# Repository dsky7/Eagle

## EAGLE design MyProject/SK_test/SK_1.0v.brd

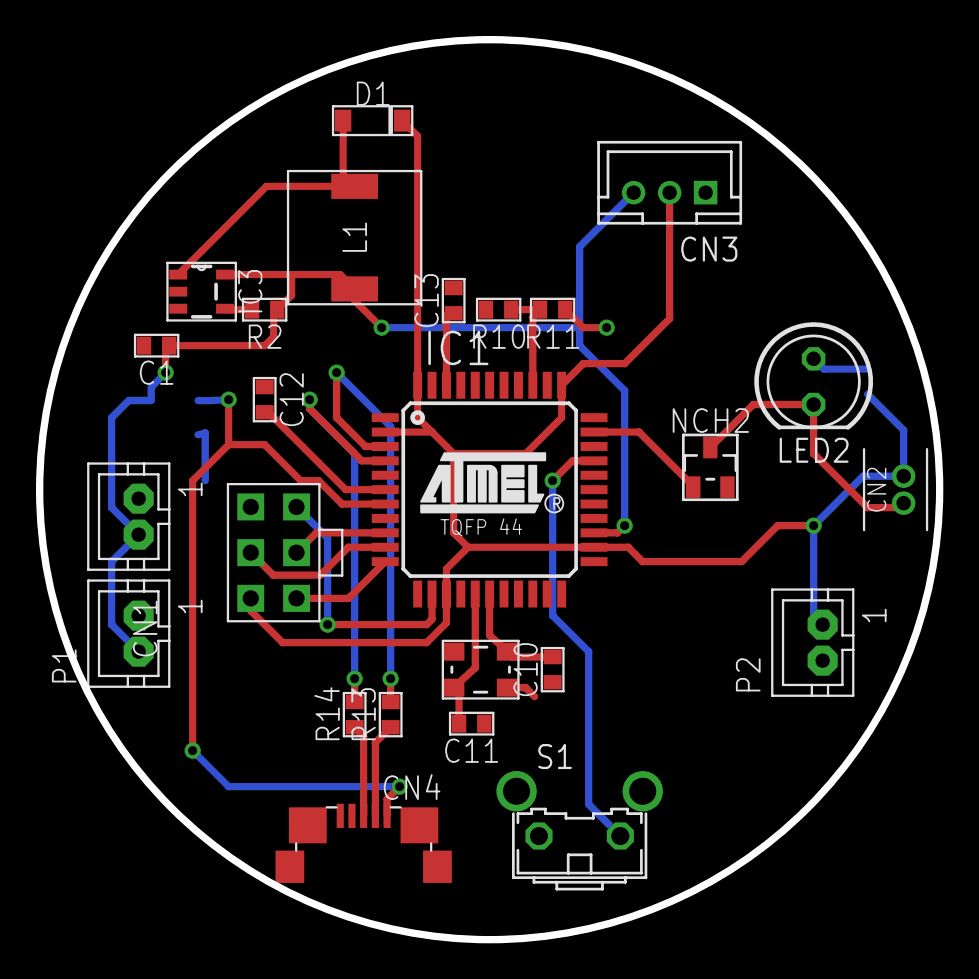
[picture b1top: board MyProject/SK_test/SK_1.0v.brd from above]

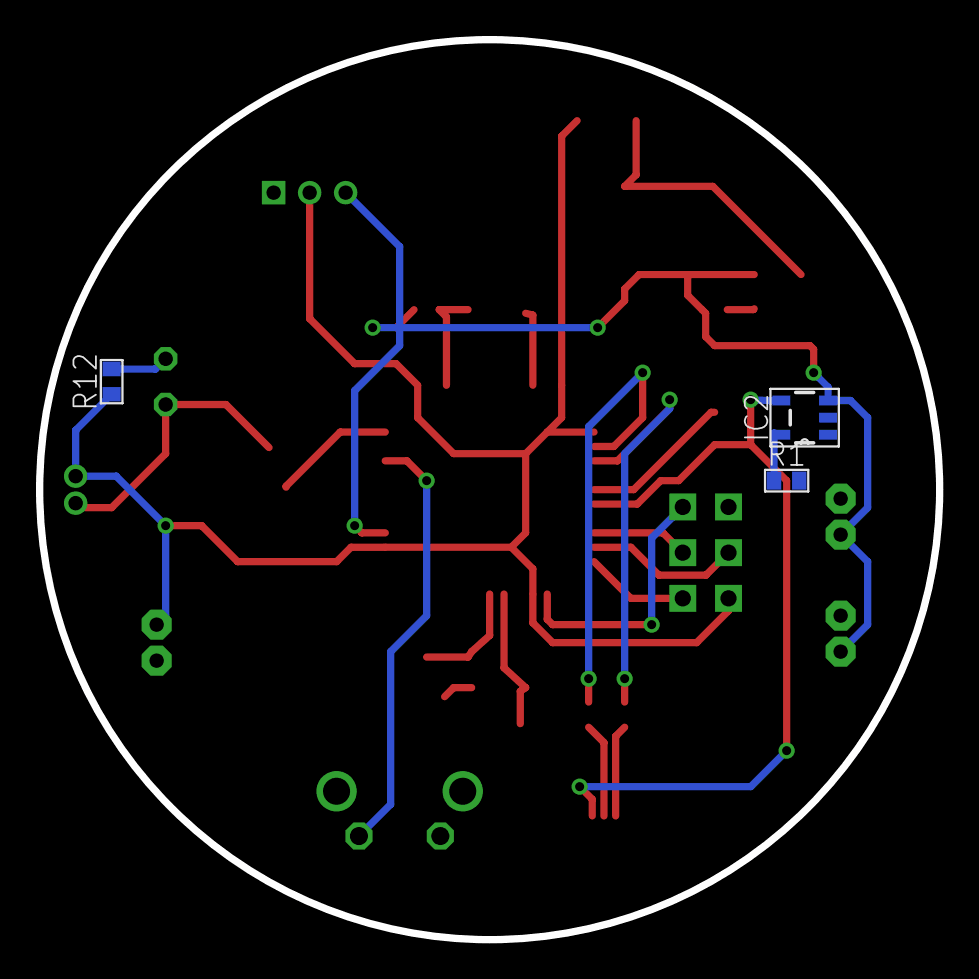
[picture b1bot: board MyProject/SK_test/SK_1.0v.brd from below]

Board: 2 copper layers, 50.0 x 50.0 mm, 28 parts (3 on the bottom side), 25 nets.

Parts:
C1, C10, C11, C12, C13: 1608
CN1: JST-PH2
CN2: B2B-ZR
CN3: B3B-PH-K-S
CN4: MICRO-USB-SHIELD-ZX62R-B-5P; ZX62R-B-5P
D1: SOD-123; SOD_123
IC1: ATMEGA32U4-AU; TQFP44
IC2: MCP73831; SOT23-5L
IC3: LM2735; SOT23-5L
L1: D63; TOKO
LED2: 5MMLED; 5MM
NCH2: CHIP_FET; SOT23
P1, P2: JST-PH2
R1, R2, R10, R11, R12, R13, R14: 1608
S1: B3F-31XX
U$3: ICSP
U$46: FA-238

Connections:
+3.7V: C1.P$1, CN1.2, IC2.3, IC3.5, L1.1, P1.2, R2.2, R11.2
+5V: CN2.1, CN3.2, D1.C, IC1.2, IC1.14, IC1.24, IC1.34, IC1.44, P2.1, R12.2, U$3.2
+USB5V: CN4.1, IC1.7, IC2.4
ADC0: IC1.36, R10.2, R11.1
D4: CN3.3, IC1.25
D10: IC1.30, S1.2
D13: IC1.32, NCH2.1
D+: CN4.3, R14.2
D-: CN4.2, R13.2
GND: C1.P$2, C10.P$1, C11.P$1, C12.P$1, C13.P$2, CN1.1, CN3.1, CN4.5, IC1.5, IC1.15, IC1.23, IC1.35, IC1.43, IC2.2, IC3.2, NCH2.2, P1.1, P2.2, R1.1, R10.1, S1.1, U$3.6, U$46.2, U$46.4
MISO: IC1.11, U$3.1
MOSI: IC1.10, U$3.4
unnamed: CN2.2, LED2.K, NCH2.3
unnamed: IC2.5, R1.2
unnamed: IC3.4, R2.1
unnamed: D1.A, IC3.1, L1.2
unnamed: IC1.3, R13.1
unnamed: C13.P$1, IC1.42
unnamed: C10.P$2, IC1.17, U$46.1
unnamed: LED2.A, R12.1
unnamed: C11.P$2, IC1.16, U$46.3
unnamed: IC1.4, R14.1
unnamed: C12.P$2, IC1.6
RESET: IC1.13, U$3.5
SCLK: IC1.9, U$3.3

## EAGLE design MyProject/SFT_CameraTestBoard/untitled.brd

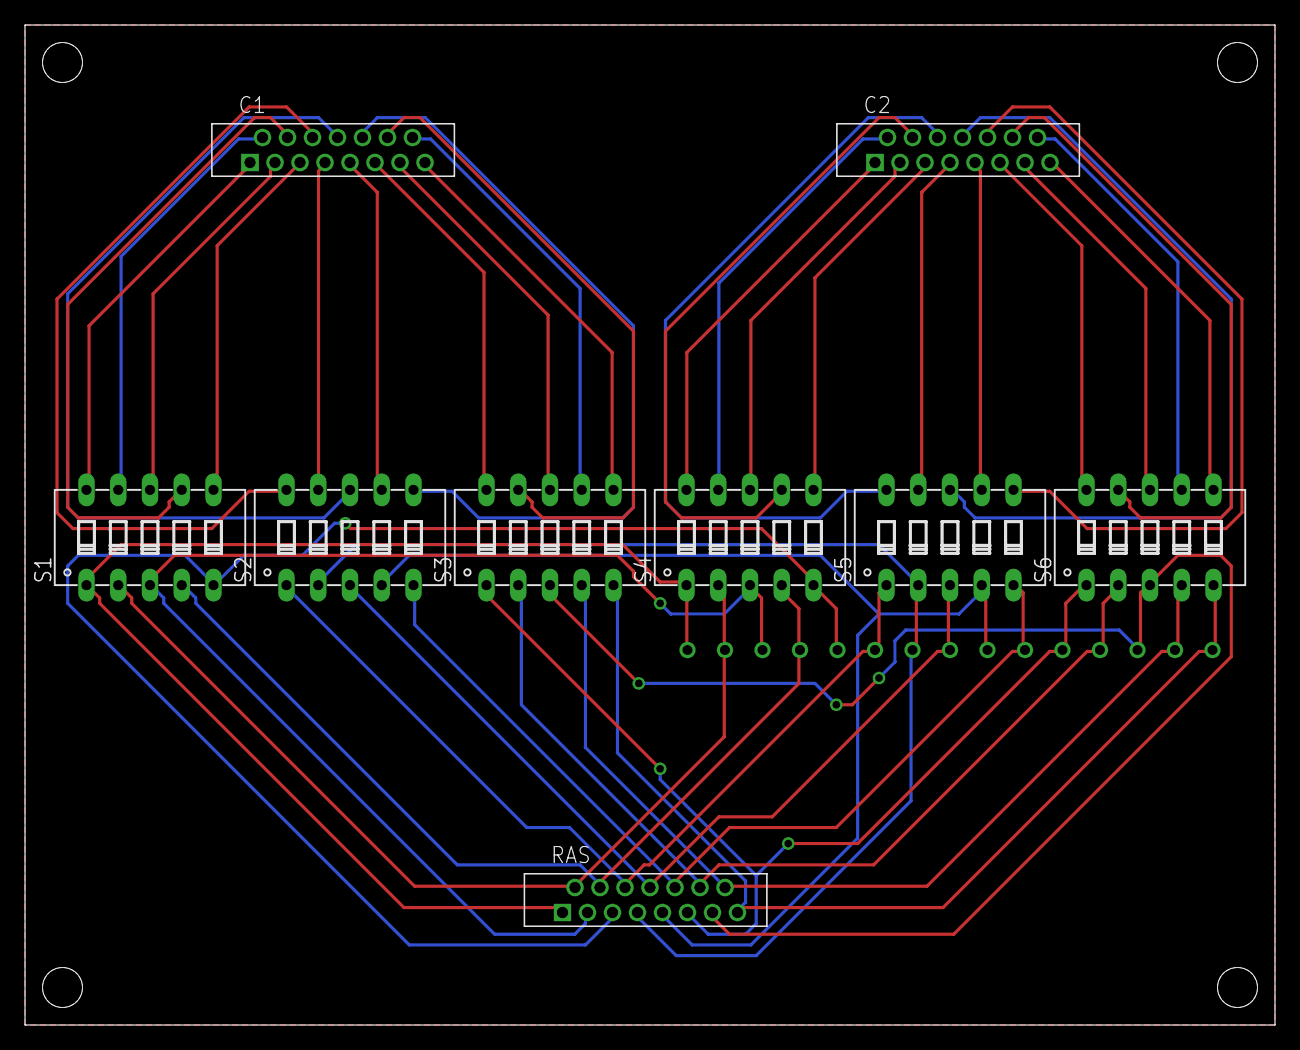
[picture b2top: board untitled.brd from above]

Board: 2 copper layers, 100.0 x 80.0 mm, 24 parts (0 on the bottom side), 45 nets.

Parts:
C1, C2: FMZ15
RAS: FMZ15
S1, S2, S3, S4, S5, S6: DIP05YL
U$4, U$5, U$6, U$7, U$8, U$9, U$10, U$11, U$12, U$13, U$14, U$15, U$16, U$17, U$18: CHECK_0.8MM

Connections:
2: RAS.2, S1.2, S4.2, U$5.P$1
3: RAS.3, S1.3, S4.3, U$6.P$1
4: RAS.4, S1.4, S4.4, U$7.P$1
5: RAS.5, S1.5, S4.5, U$8.P$1
6: RAS.6, S2.1, S5.1, U$9.P$1
7: RAS.7, S2.2, S5.2, U$10.P$1
8: RAS.8, S2.3, S5.3, U$11.P$1
9: RAS.9, S2.4, S5.4, U$12.P$1
10: RAS.10, S2.5, S5.5, U$13.P$1
11: RAS.11, S3.1, S6.1, U$14.P$1
12: RAS.12, S3.2, S6.2, U$15.P$1
13: RAS.13, S3.3, S6.3, U$16.P$1
14: RAS.14, S3.4, S6.4, U$17.P$1
15: RAS.15, S3.5, S6.5, U$18.P$1
GND: RAS.1, S1.1, S4.1, U$4.P$1
unnamed: C1.1, S1.10
unnamed: C1.2, S1.9
unnamed: C1.3, S1.8
unnamed: C1.4, S1.7
unnamed: C1.5, S1.6
unnamed: C1.10, S2.6
unnamed: C1.9, S2.7
unnamed: C1.8, S2.8
unnamed: C1.7, S2.9
unnamed: C1.6, S2.10
unnamed: C1.15, S3.6
unnamed: C1.14, S3.7
unnamed: C1.13, S3.8
unnamed: C1.12, S3.9
unnamed: C1.11, S3.10
unnamed: C2.5, S4.6
unnamed: C2.4, S4.7
unnamed: C2.3, S4.8
unnamed: C2.2, S4.9
unnamed: C2.1, S4.10
unnamed: C2.10, S5.6
unnamed: C2.9, S5.7
unnamed: C2.8, S5.8
unnamed: C2.7, S5.9
unnamed: C2.6, S5.10
unnamed: C2.15, S6.6
unnamed: C2.14, S6.7
unnamed: C2.13, S6.8
unnamed: C2.12, S6.9
unnamed: C2.11, S6.10

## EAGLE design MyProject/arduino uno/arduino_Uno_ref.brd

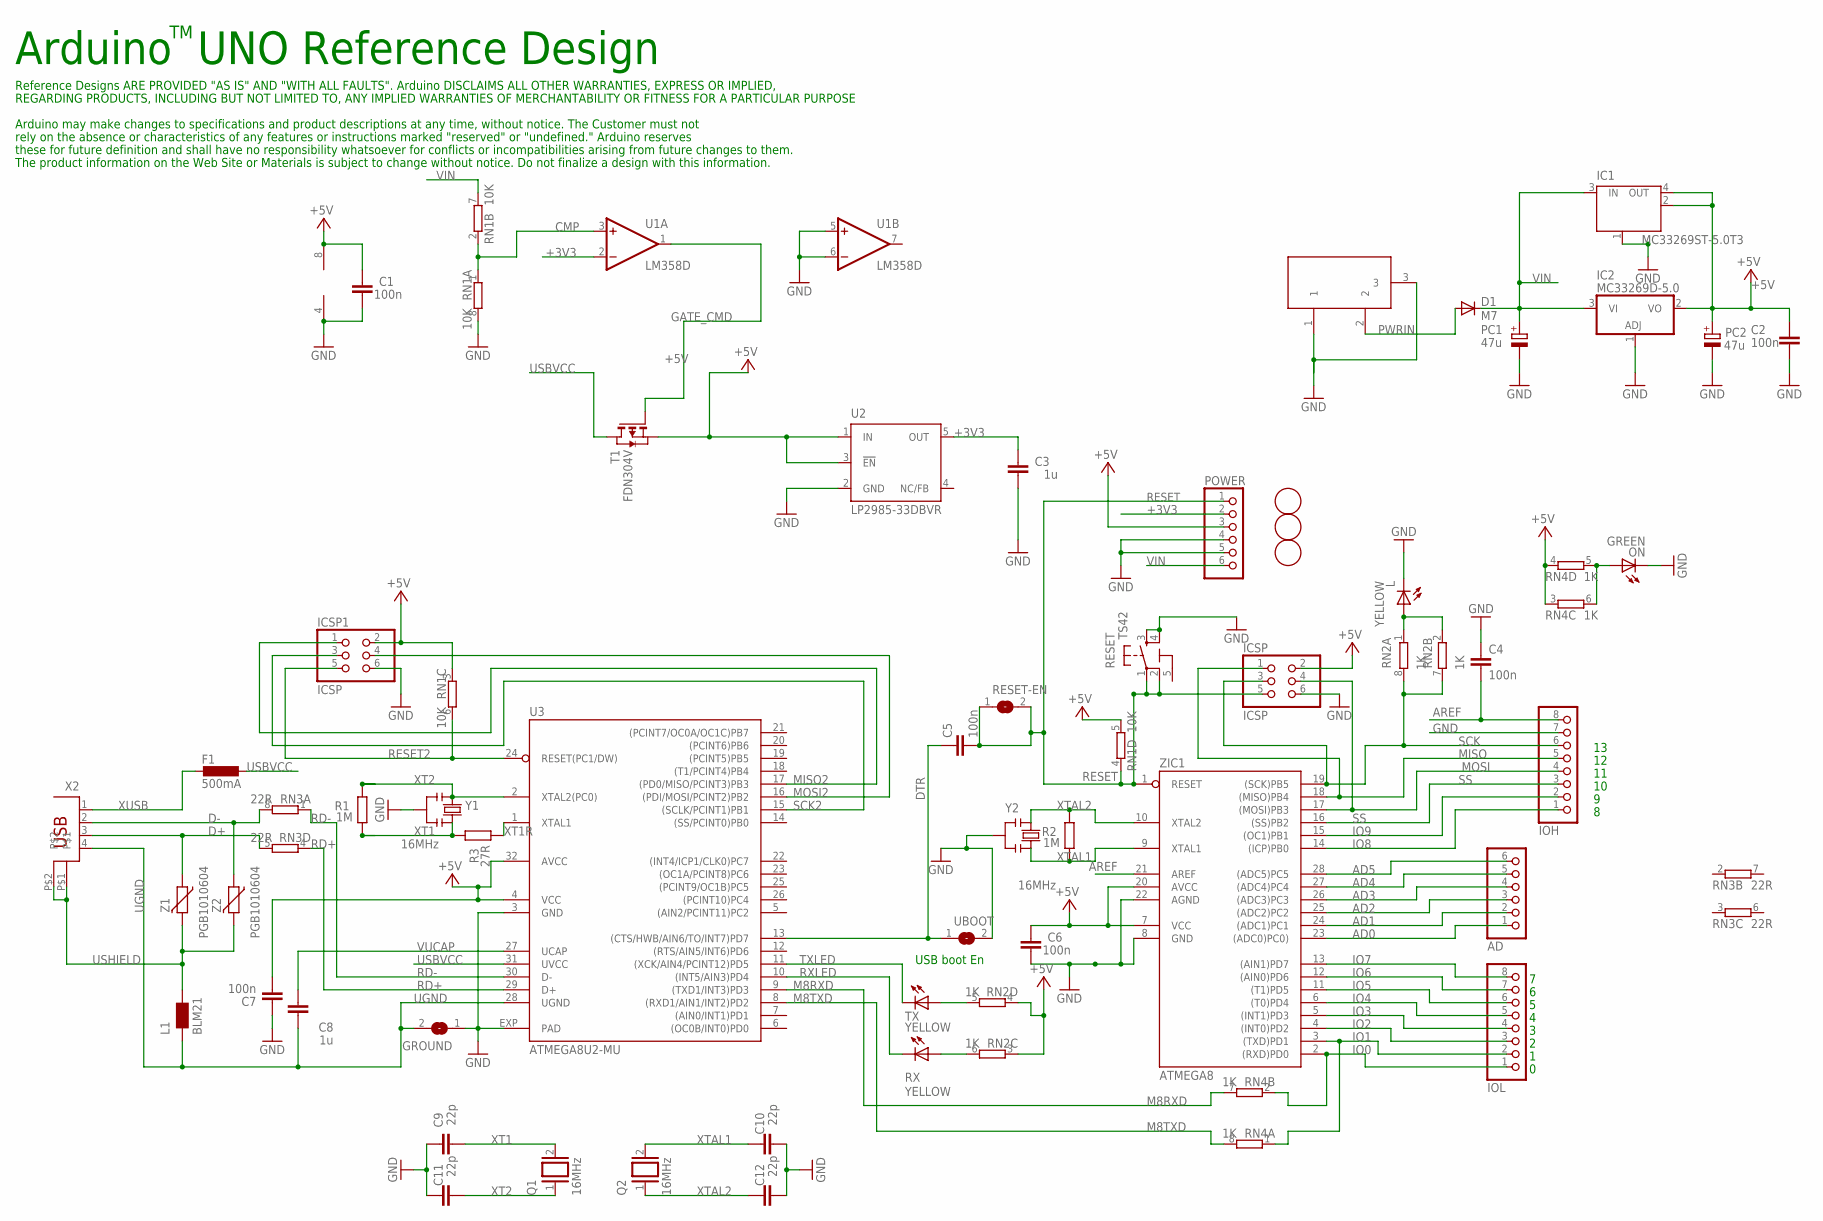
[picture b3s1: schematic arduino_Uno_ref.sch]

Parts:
AD: PINHD-1X6; 1X06
C1, C2, C4, C5, C6, C7: 100n; C0603-ROUND
C3, C8: 1u; C0603-ROUND
C9, C10, C11, C12: 22p; C0603-ROUND
D1: M7; SMB
F1: 500mA; L1812
GROUND: SJ
IC1: MC33269ST-5.0T3; SOT223
IC2: MC33269D-5.0; DPACK
ICSP, ICSP1: ICSP; 2X03
IOH: PINHD-1X8; 1X08
IOL: PINHD-1X8; 1X08
L: YELLOW; CHIP-LED0805
L1: BLM21; 0805
ON: GREEN; CHIP-LED0805
PC1, PC2: 47u; PANASONIC_D
POWER: PINHD-1X6; 1X06
Q1, Q2: 16MHz; QS
R1, R2: 1M; R0603-ROUND
R3: 27R; R0603-ROUND
RESET: TS42
RESET-EN: SJ
RN1: 10K; CAY16
RN2, RN4: 1K; CAY16
RN3: 22R; CAY16
RX: YELLOW; CHIP-LED0805
T1: FDN304V; SOT-23
TX: YELLOW; CHIP-LED0805
U1: LM358D; SO08
U2: LP2985-33DBVR; SOT23-DBV
U3: ATMEGA8U2-MU; QFN32
U$3, U$4, U$6: FIDUCIALMOUNT; FIDUCIA-MOUNT
UBOOT: SJ
X1: DC21MMX; DC-21MM
X2: PN61729
Y1, Y2: 16MHz; RESONATOR
Z1, Z2: PGB1010604; CT/CN0603
ZIC1: ATMEGA8; DIL28-3

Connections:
5-GND: RESET.5 (5-GND)
+3V3: C3.2, POWER.2, U1.2 (-IN), U2.5 (OUT)
+5V: C1.2, C2.2, C6.2, C7.1, IC1.2 (OUT), IC1.4 (OUT), IC2.2 (VO), ICSP.2, ICSP1.2, PC2.+, POWER.3, RN1.3 (1), RN1.5 (2), RN2.3 (1), RN2.4 (1), RN4.3 (1), RN4.4 (1), T1.2 (S), U1.8 (V+), U2.1 (IN), U2.3 (!EN), U3.4 (VCC), U3.32 (AVCC), ZIC1.7 (VCC), ZIC1.20 (AVCC)
AD0: AD.1, ZIC1.23 ((ADC0)PC0))
AD1: AD.2, ZIC1.24 ((ADC1)PC1)
AD2: AD.3, ZIC1.25 ((ADC2)PC2)
AD3: AD.4, ZIC1.26 ((ADC3)PC3)
AD4: AD.5, ZIC1.27 ((ADC4)PC4)
AD5: AD.6, ZIC1.28 ((ADC5)PC5)
AREF: C4.2, IOH.8, ZIC1.21 (AREF)
CMP: RN1.1, RN1.2 (1), U1.3 (+IN)
D+: RN3.5 (2), X2.3, Z1.1
D-: RN3.8 (2), X2.2, Z2.1
DTR: C5.1, U3.13 ((CTS/HWB/AIN6/TO/INT7)PD7), UBOOT.1
GATE_CMD: T1.3 (G), U1.1 (OUT)
GND: C1.1, C2.1, C3.1, C4.1, C6.1, C7.2, C9.2, C10.1, C11.2, C12.1, GROUND.1, IC1.1 (GND/ADJ), IC2.1 (ADJ), ICSP.6, ICSP1.6, IOH.7, L.C, ON.C, PC1.-, PC2.-, POWER.4, POWER.5, RESET.3, RESET.4, RN1.8 (2), U1.4 (V-), U1.5 (+IN), U1.6 (-IN), U2.2 (GND), U3.3 (GND), U3.EXP (PAD), UBOOT.2, X1.1, X1.3, Y1.2, Y2.2, ZIC1.8 (GND), ZIC1.22 (AGND)
IO0: IOL.1, RN4.2 (1), ZIC1.2 ((RXD)PD0)
IO1: IOL.2, RN4.1, ZIC1.3 ((TXD)PD1)
IO2: IOL.3, ZIC1.4 ((INT0)PD2)
IO3: IOL.4, ZIC1.5 ((INT1)PD3)
IO4: IOL.5, ZIC1.6 ((T0)PD4)
IO5: IOL.6, ZIC1.11 ((T1)PD5)
IO6: IOL.7, ZIC1.12 ((AIN0)PD6)
IO7: IOL.8, ZIC1.13 ((AIN1)PD7)
IO8: IOH.1, ZIC1.14 ((ICP)PB0)
IO9: IOH.2, ZIC1.15 ((OC1)PB1)
M8RXD: RN4.7 (2), U3.9 ((TXD1/INT3)PD3)
M8TXD: RN4.8 (2), U3.8 ((RXD1/AIN1/INT2)PD2)
MISO: ICSP.1, IOH.5, ZIC1.18 ((MISO)PB4)
MISO2: ICSP1.1, U3.17 ((PD0/MISO/PCINT3)PB3)
MOSI: ICSP.4, IOH.4, ZIC1.17 ((MOSI)PB3)
MOSI2: ICSP1.4, U3.16 ((PDI/MOSI/PCINT2)PB2)
unnamed: L.A, RN2.1, RN2.2 (1)
unnamed: ON.A, RN4.5 (2), RN4.6 (2)
unnamed: RN2.6 (2), RX.A
unnamed: RN2.5 (2), TX.A
PWRIN: D1.A, X1.2
RD+: RN3.4 (1), U3.29 (D+)
RD-: RN3.1, U3.30 (D-)
RESET: C5.2, ICSP.5, POWER.1, RESET.1, RESET.2, RESET-EN.1, RESET-EN.2, RN1.4 (1), ZIC1.1 (RESET)
RESET2: ICSP1.5, RN1.6 (2), U3.24 (RESET(PC1/DW))
RXLED: RX.C, U3.10 ((INT5/AIN3)PD4)
SCK: ICSP.3, IOH.6, RN2.7 (2), RN2.8 (2), ZIC1.19 ((SCK)PB5)
SCK2: ICSP1.3, U3.15 ((SCLK/PCINT1)PB1)
SS: IOH.3, ZIC1.16 ((SS)PB2)
TXLED: TX.C, U3.11 ((XCK/AIN4/PCINT12)PD5)
UGND: C8.2, GROUND.2, L1.1, U3.28 (UGND), X2.4
USBVCC: F1.1, T1.1 (D), U3.31 (UVCC)
USHIELD: L1.2, X2.P$1, X2.P$2, Z1.2, Z2.2
VIN: D1.C, IC1.3 (IN), IC2.3 (VI), PC1.+, POWER.6, RN1.7 (2)
VUCAP: C8.1, U3.27 (UCAP)
XT1: C9.1, Q1.2, R1.1, R3.2, Y1.3
XT1R: R3.1, U3.1 (XTAL1)
XT2: C11.1, Q1.1, R1.2, U3.2 (XTAL2(PC0)), Y1.1
XTAL1: C10.2, Q2.2, R2.1, Y2.3, ZIC1.9 (XTAL1)
XTAL2: C12.2, Q2.1, R2.2, Y2.1, ZIC1.10 (XTAL2)
XUSB: F1.2, X2.1

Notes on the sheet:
Arduino UNO Reference Design
USB boot En
Reference Designs ARE PROVIDED "AS IS" AND "WITH ALL FAULTS". Arduino DISCLAIMS ALL OTHER WARRANTIES, EXPRESS OR IMPLIED,
Arduino may make changes to specifications and product descriptions at any time, without notice. The Customer must not
REGARDING PRODUCTS, INCLUDING BUT NOT LIMITED TO, ANY IMPLIED WARRANTIES OF MERCHANTABILITY OR FITNESS FOR A PARTICULAR PURPOSE
rely on the absence or characteristics of any features or instructions marked "reserved" or "undefined." Arduino reserves
these for future definition and shall have no responsibility whatsoever for conflicts or incompatibilities arising from future changes to them.
The product information on the Web Site or Materials is subject to change without notice. Do not finalize a design with this information.

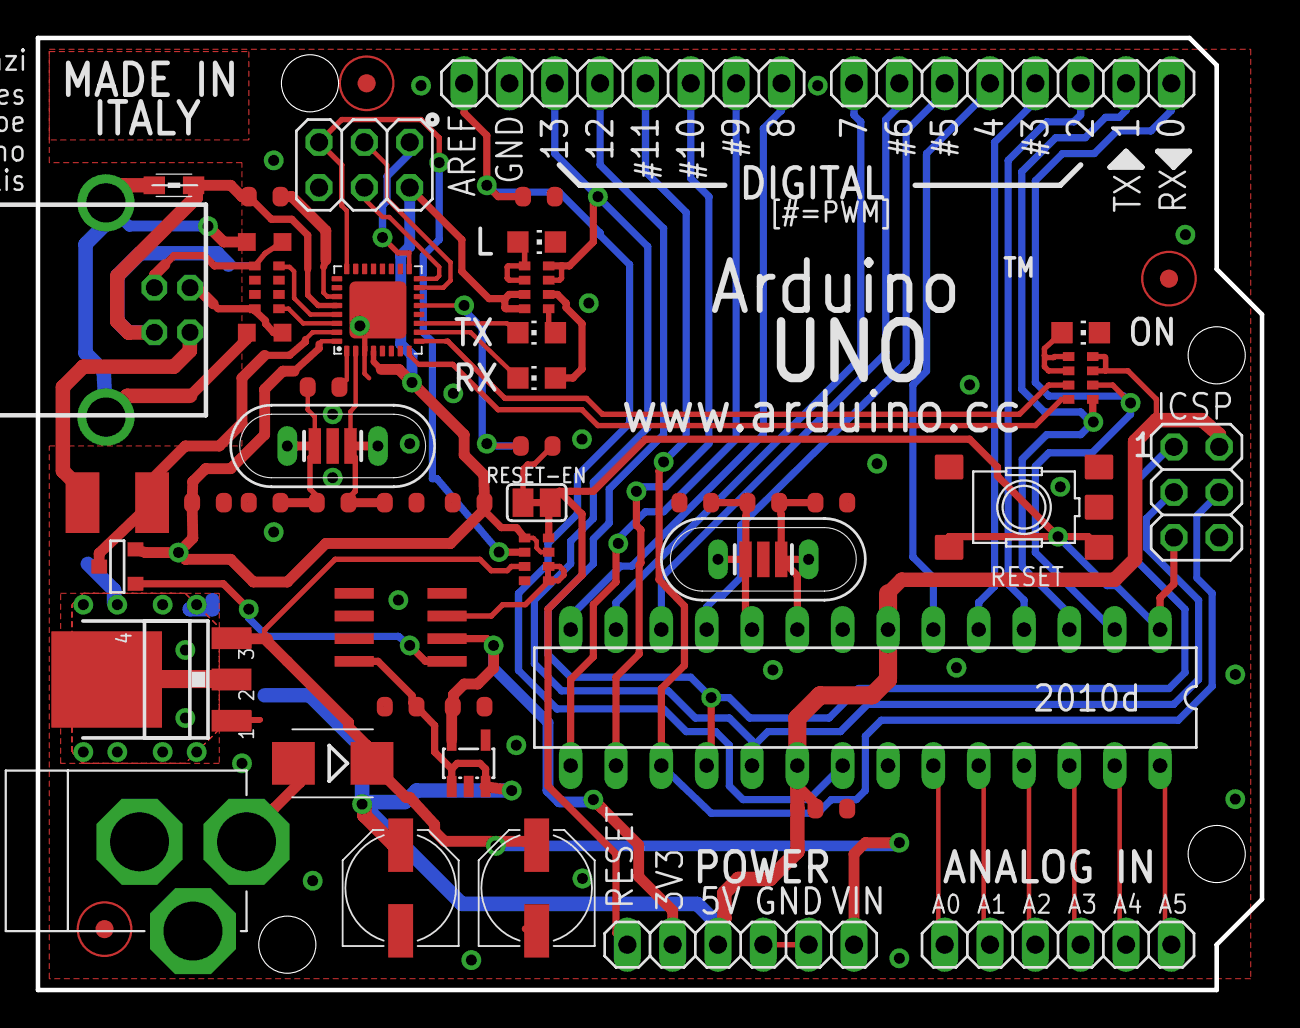
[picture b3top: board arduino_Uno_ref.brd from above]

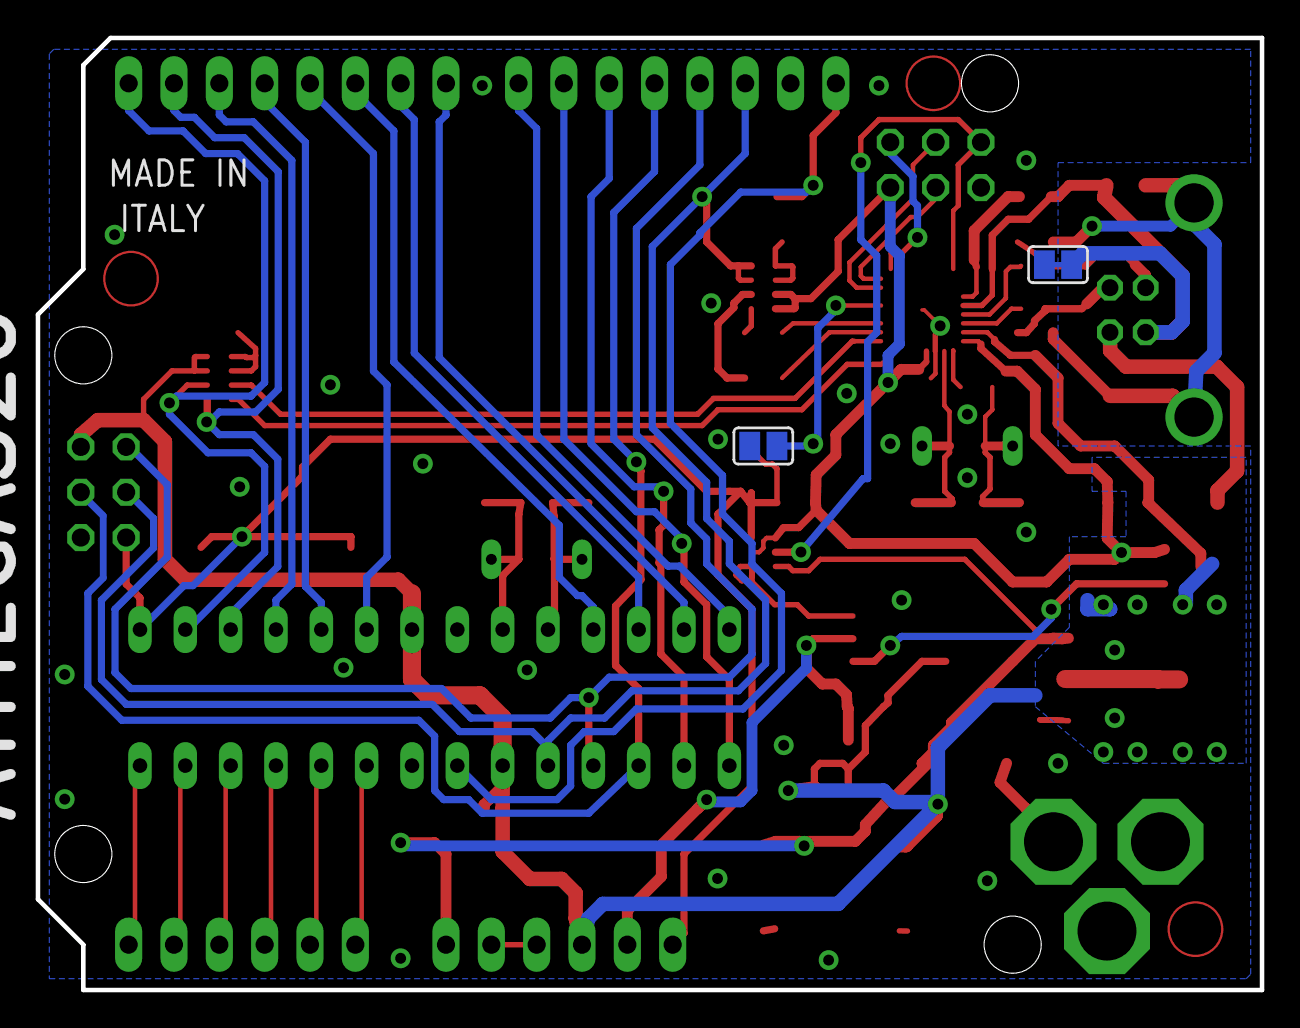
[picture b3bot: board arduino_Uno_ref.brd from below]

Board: 2 copper layers, 68.6 x 53.3 mm, 56 parts (2 on the bottom side), 56 nets.

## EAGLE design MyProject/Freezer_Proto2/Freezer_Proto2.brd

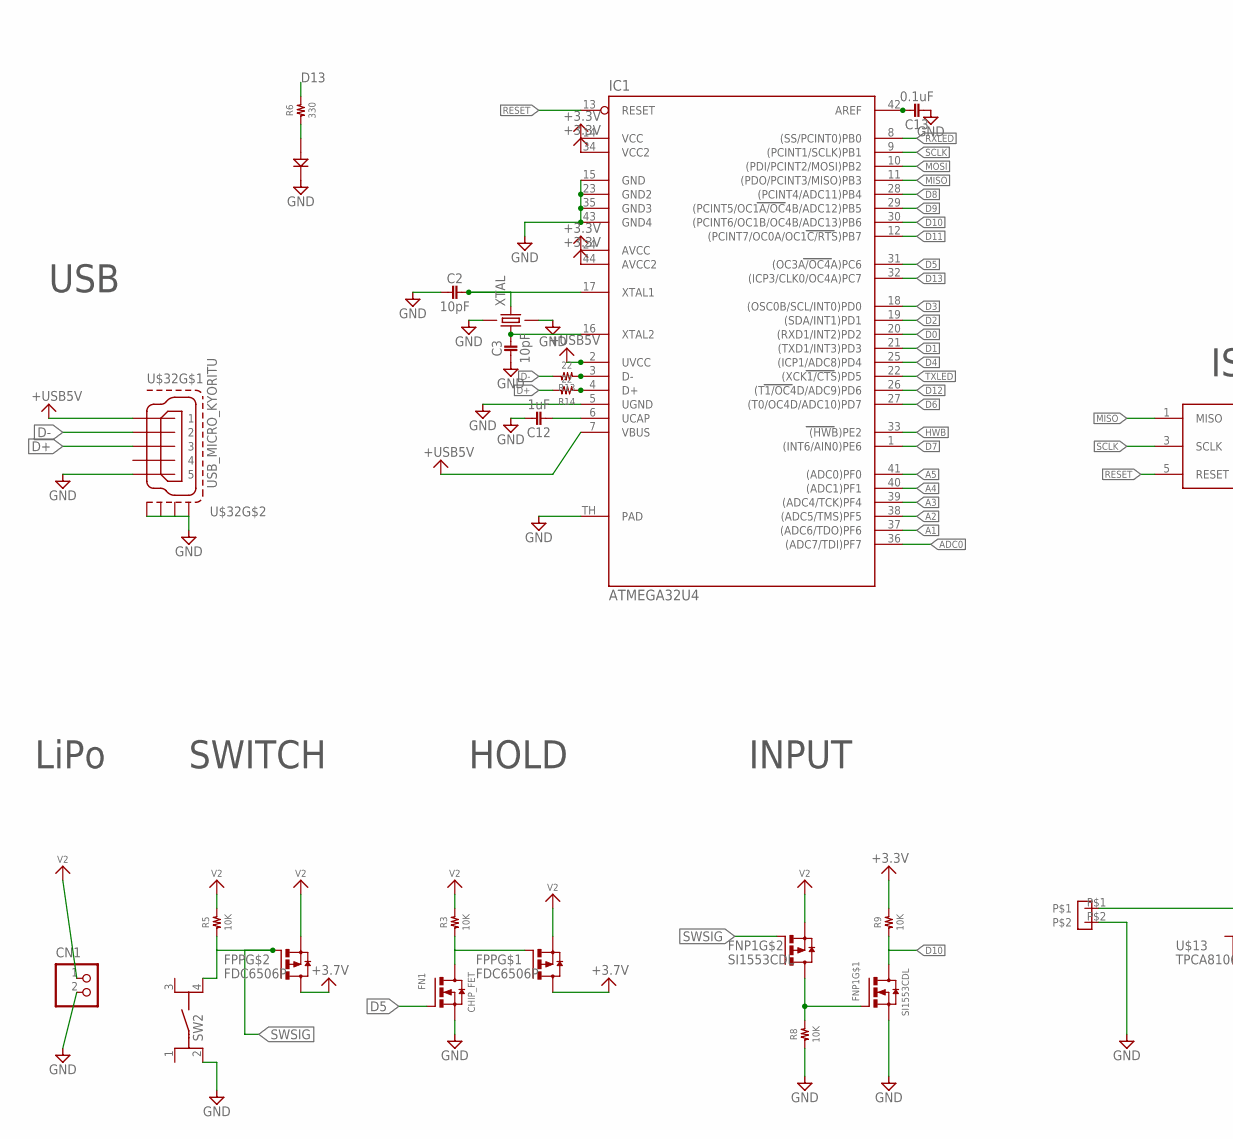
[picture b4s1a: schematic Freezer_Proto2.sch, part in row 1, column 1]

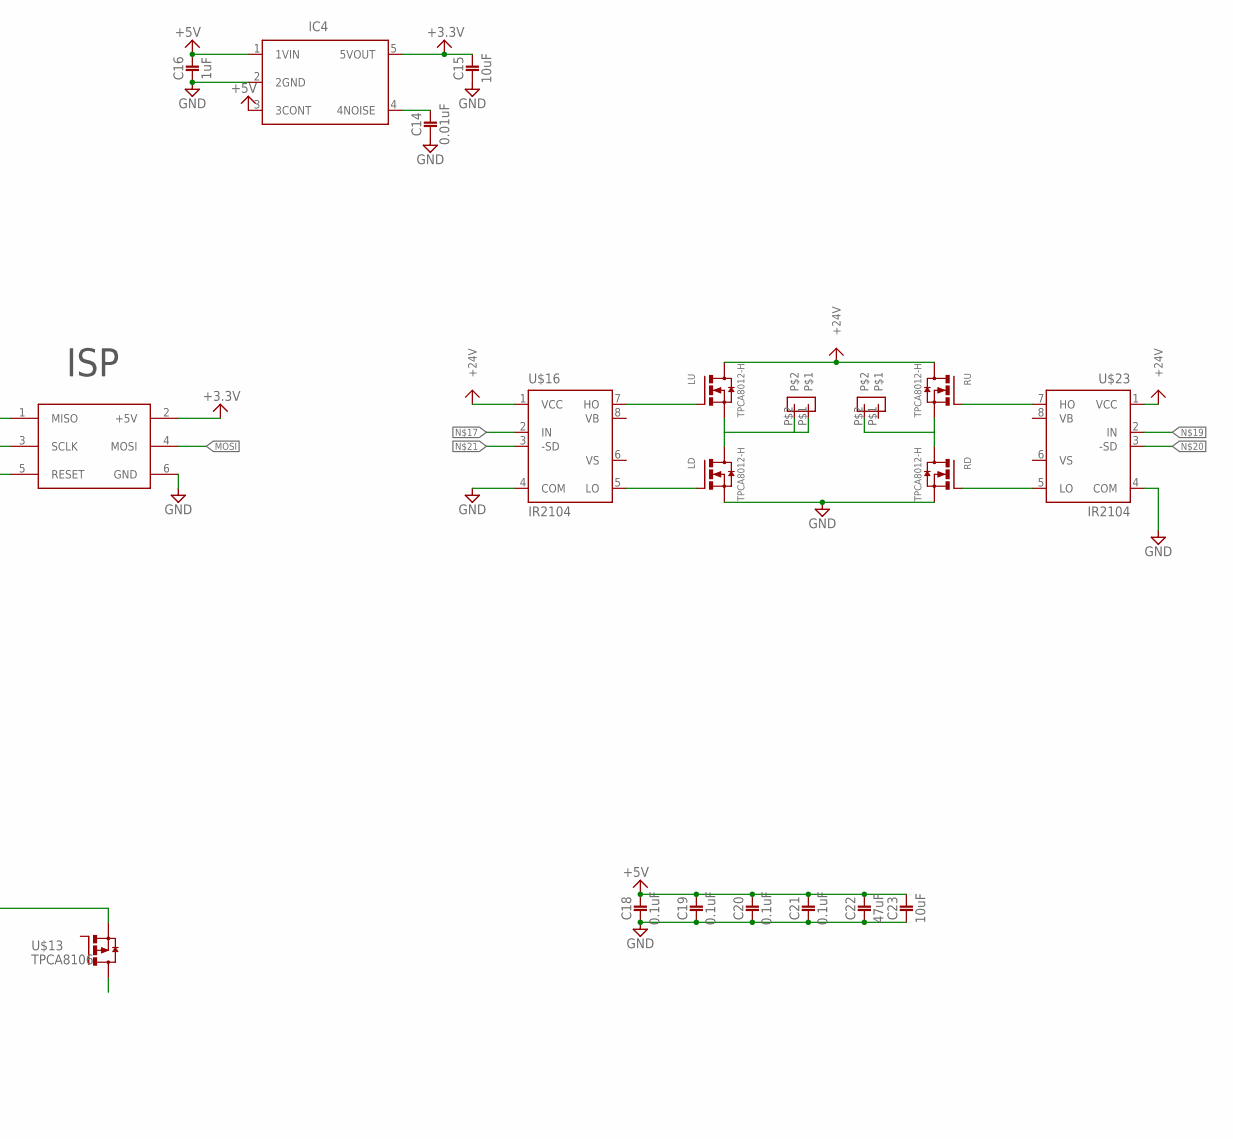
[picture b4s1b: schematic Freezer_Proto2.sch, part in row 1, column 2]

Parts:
C2, C3: 10pF; 1005
C12, C16: 1uF; 1005
C13, C18, C19, C20, C21: 0.1uF; 1005
C14: 0.01uF; 1608
C15, C23: 10uF; 1608
C22: 47uF; 1608
CN1: S2B-PH-K-S
FN1: CHIP_FET; SOT23
FNP1: SI1553CDL; SOT363
FPP: FDC6506P; SOT23-6
IC1: ATMEGA32U4; QFN-44-7X7
IC4: TAR5SB; SSOP5-P-0.95
LD: TPCA8012-H; 2-5Q1A
LED1: 1608
LU: TPCA8012-H; 2-5Q1A
R3, R5, R8, R9: 10K; 1005
R6: 330; 1005
R13, R14: 22; 1005
RD: TPCA8012-H; 2-5Q1A
RU: TPCA8012-H; 2-5Q1A
SW2: SKRPACE010; SKRP
U$3: ICSP
U$7, U$38, U$43: TERMINAL_2P
U$13: TPCA8106; 2-5Q1A
U$16, U$23: IR2104; SOIC8
U$32: USB_MICRO_KYORITU
XTAL: FA-238

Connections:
+3.3V: C15.P$1 (1), IC1.14 (VCC), IC1.24 (AVCC), IC1.34 (VCC2), IC1.44 (AVCC2), IC4.5 (5VOUT), R9.2, U$3.2 (+5V)
+3.7V: FPP.4 (D), FPP.6 (D)
+5V: C16.1, C18.1, C19.1, C20.1, C21.1, C22.P$1 (1), C23.P$1 (1), IC4.1 (1VIN), IC4.3 (3CONT)
+24V: LU.5 (D), LU.6 (D), LU.7 (D), LU.8 (D), RU.5 (D), RU.6 (D), RU.7 (D), RU.8 (D), U$16.1 (VCC), U$23.1 (VCC)
+USB5V: IC1.2 (UVCC), IC1.7 (VBUS), U$32.1
A1: IC1.37 ((ADC6/TDO)PF6)
A2: IC1.38 ((ADC5/TMS)PF5)
A3: IC1.39 ((ADC4/TCK)PF4)
A4: IC1.40 ((ADC1)PF1)
A5: IC1.41 ((ADC0)PF0)
ADC0: IC1.36 ((ADC7/TDI)PF7)
D0: IC1.20 ((RXD1/INT2)PD2)
D1: IC1.21 ((TXD1/INT3)PD3)
D2: IC1.19 ((SDA/INT1)PD1)
D3: IC1.18 ((OSC0B/SCL/INT0)PD0)
D4: IC1.25 ((ICP1/ADC8)PD4)
D5: FN1.1 (G), IC1.31 ((OC3A/OC4A)PC6)
D6: IC1.27 ((T0/OC4D/ADC10)PD7)
D7: IC1.1 ((INT6/AIN0)PE6)
D8: IC1.28 ((PCINT4/ADC11)PB4)
D9: IC1.29 ((PCINT5/OC1A/OC4B/ADC12)PB5)
D10: FNP1.6 (D), IC1.30 ((PCINT6/OC1B/OC4B/ADC13)PB6), R9.1
D11: IC1.12 ((PCINT7/OC0A/OC1C/RTS)PB7)
D12: IC1.26 ((T1/OC4D/ADC9)PD6)
D13: IC1.32 ((ICP3/CLK0/OC4A)PC7), R6.2
D+: R14.2, U$32.3
D-: R13.2, U$32.2
GND: C2.2, C3.2, C12.1, C13.2, C14.P$2 (2), C15.P$2 (2), C16.2, C18.2, C19.2, C20.2, C21.2, C22.P$2 (2), C23.P$2 (2), CN1.2, FN1.2 (S), FNP1.1 (S), IC1.5 (UGND), IC1.15 (GND), IC1.23 (GND2), IC1.35 (GND3), IC1.43 (GND4), IC1.TH (PAD), IC4.2 (2GND), LD.1 (S), LD.2 (S), LD.3 (S), LED1.2 (K), R8.1, RD.1 (S), RD.2 (S), RD.3 (S), SW2.2 (1_), U$3.6 (GND), U$7.P$2, U$16.4 (COM), U$23.4 (COM), U$32.5, U$32.M1 (S1), U$32.M2 (S2), U$32.M3 (S3), U$32.M4 (S4), XTAL.2, XTAL.4
HWB: IC1.33 ((HWB)PE2)
MISO: IC1.11 ((PDO/PCINT3/MISO)PB3), U$3.1 (MISO)
MOSI: IC1.10 ((PDI/PCINT2/MOSI)PB2), U$3.4 (MOSI)
unnamed: LED1.1 (A), R6.1
unnamed: U$7.P$1, U$13.1 (S), U$13.2 (S), U$13.3 (S)
unnamed: RU.4 (G), U$23.7 (HO)
unnamed: U$13.5 (D), U$13.6 (D), U$13.7 (D), U$13.8 (D)
unnamed: FN1.3 (D), FPP.1 (G), R3.1
unnamed: C3.1, IC1.16 (XTAL2), XTAL.1
unnamed: IC1.3 (D-), R13.1
unnamed: C13.1, IC1.42 (AREF)
unnamed: C2.1, IC1.17 (XTAL1), XTAL.3
unnamed: RD.4 (G), U$23.5 (LO)
unnamed: LU.4 (G), U$16.7 (HO)
unnamed: IC1.4 (D+), R14.1
unnamed: LD.4 (G), U$16.5 (LO)
unnamed: C14.P$1 (1), IC4.4 (4NOISE)
unnamed: C12.2, IC1.6 (UCAP)
P+: LD.5 (D), LD.6 (D), LD.7 (D), LD.8 (D), LU.1 (S), LU.2 (S), LU.3 (S), U$38.P$1, U$38.P$2
P-: RD.5 (D), RD.6 (D), RD.7 (D), RD.8 (D), RU.1 (S), RU.2 (S), RU.3 (S), U$43.P$2
RESET: IC1.13 (RESET), U$3.5 (RESET)
RXLED: IC1.8 ((SS/PCINT0)PB0)
SCLK: IC1.9 ((PCINT1/SCLK)PB1), U$3.3 (SCLK)
SIG: FNP1.2 (G), FNP1.3 (D), R8.2
SWSIG: FNP1.5 (G), FPP.3 (G), R5.1, SW2.4 (2_)
TXLED: IC1.22 ((XCK1/CTS)PD5)
V2: CN1.1, FNP1.4 (S), FPP.2 (S), FPP.5 (S), R3.2, R5.2

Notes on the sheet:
INPUT
HOLD
SWITCH
USB
ISP
LiPo

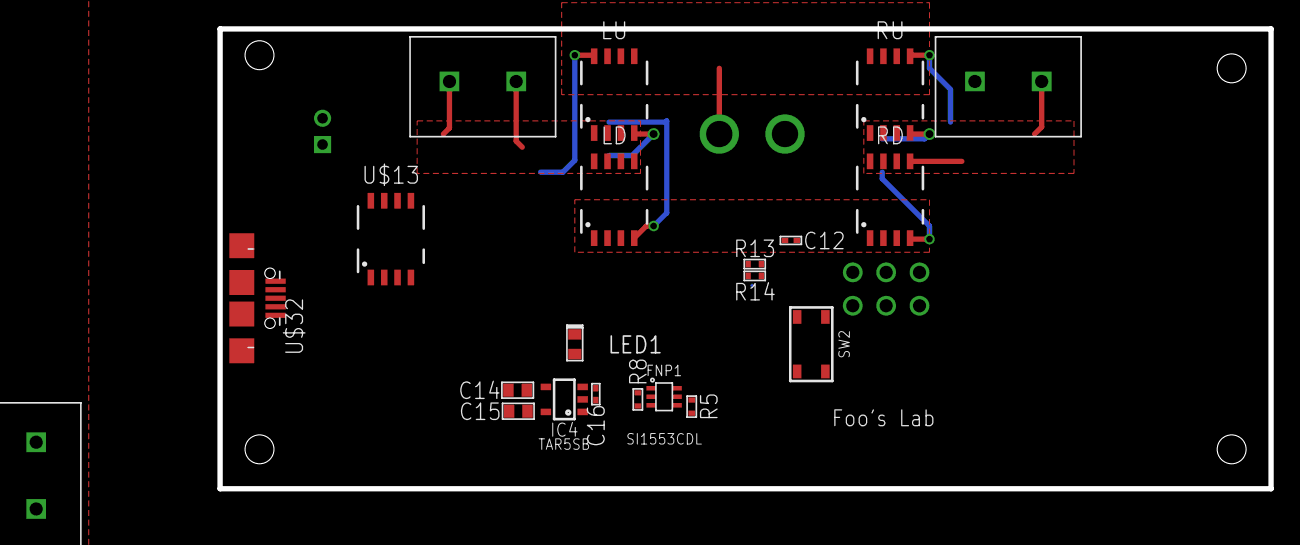
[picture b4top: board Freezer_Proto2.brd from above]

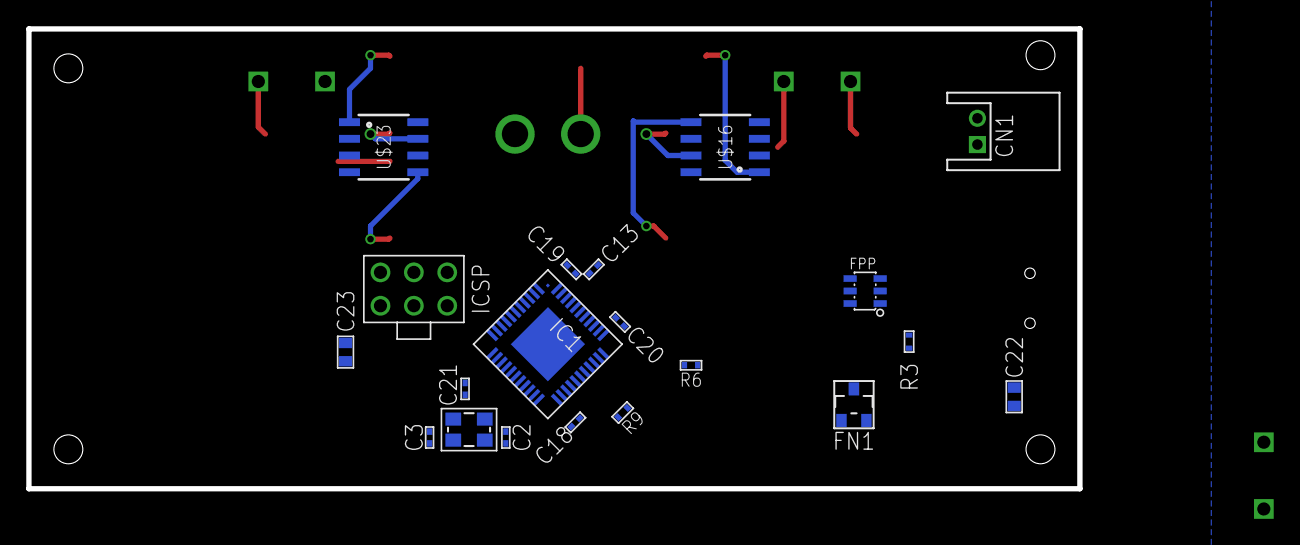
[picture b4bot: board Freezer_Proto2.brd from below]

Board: 2 copper layers, 80.0 x 35.0 mm, 41 parts (20 on the bottom side), 35 nets.
